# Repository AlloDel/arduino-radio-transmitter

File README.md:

# arduino-radio-transmitter
a simple arduino transmitter designed for an arduino quadcopter designed with kicad 5 and updated for kicad 6

images and PDF of schematic can be found in /docs directory

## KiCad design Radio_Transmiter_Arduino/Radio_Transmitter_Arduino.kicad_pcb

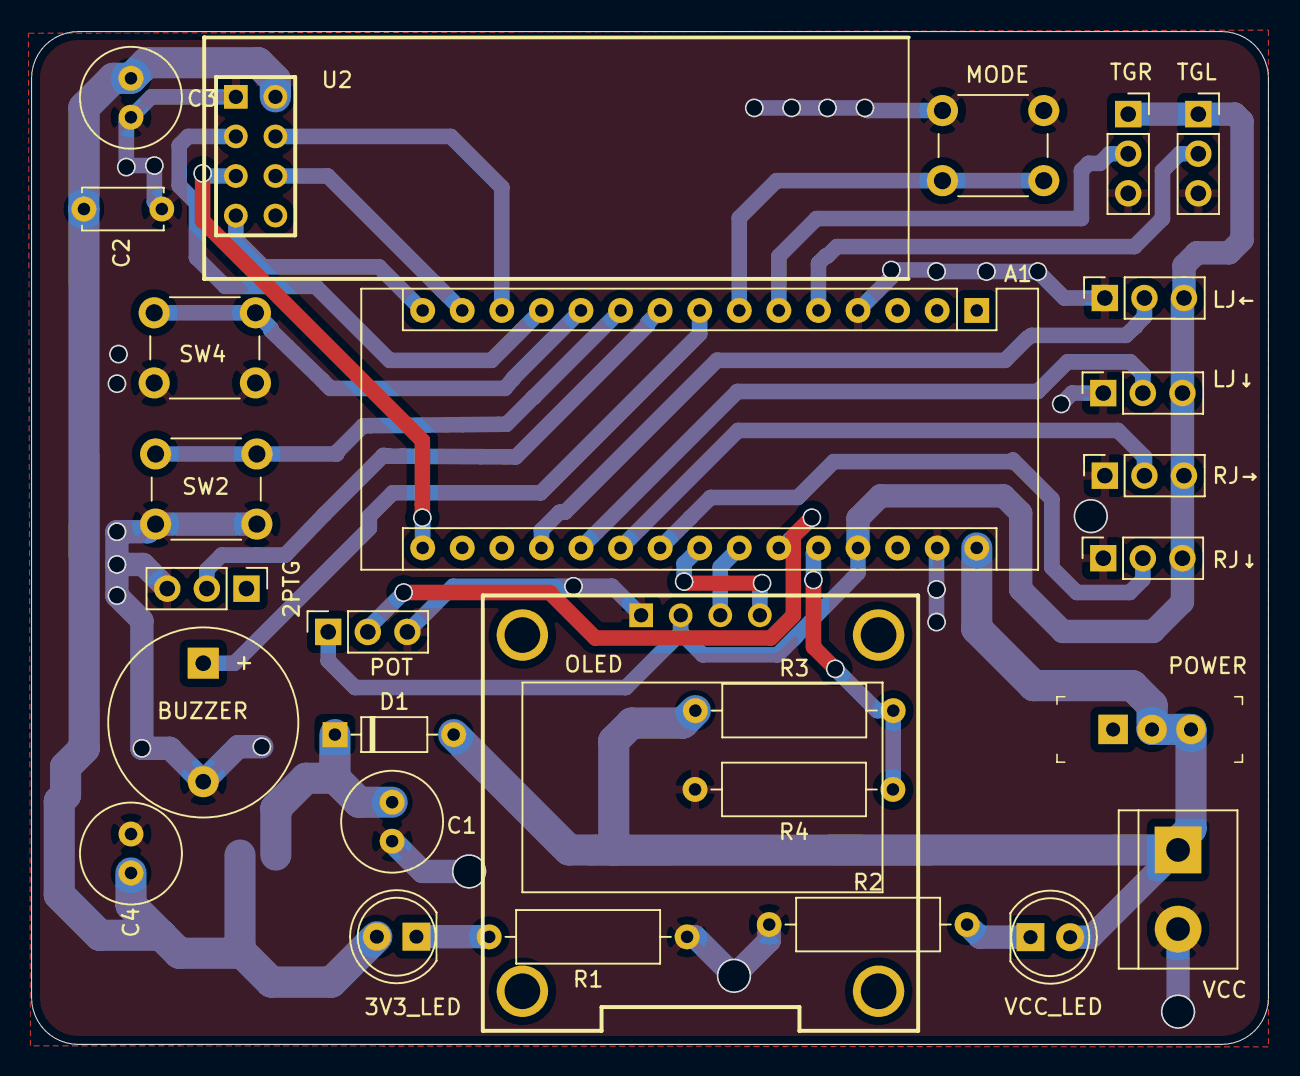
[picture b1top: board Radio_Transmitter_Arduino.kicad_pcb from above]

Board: 2 copper layers, 79.4 x 65.0 mm, 29 parts (1 on the bottom side), 27 nets.

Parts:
2PTG: SW_SPDT; PinHeader_1x03_P2.54mm_Vertical
3V3_LED: Red_LED; LED_D5.0mm_Clear
A1: Arduino_Nano_v3.x; Arduino_Nano
BUZZER: Buzzer; Buzzer_12x9.5RM7.6
C1, C3, C4: 10uF; C_Radial_D6.3mm_H11.0mm_P2.50mm
C2: 100nF; C_Disc_D5.0mm_W2.5mm_P5.00mm
D1: 1N4148; D_DO-35_SOD27_P7.62mm_Horizontal
LJ←: Conn_01x03_Male; PinSocket_1x03_P2.54mm_Vertical
LJ↓: Conn_01x03_Male; PinSocket_1x03_P2.54mm_Vertical
MODE: SW_Push; SW_PUSH_6mm_H13mm
OLED: Conn_01x04_Male; 0.96IN 128X64 I2C OLED DISPLAY MODULE (HOLES)
POT: R_POT; PinSocket_1x03_P2.54mm_Vertical
POWER: EG1218; Switch_Slide_11.6x4mm_EG1218
R1: 220; R_Axial_DIN0309_L9.0mm_D3.2mm_P12.70mm_Horizontal
R2: 330; R_Axial_DIN0309_L9.0mm_D3.2mm_P12.70mm_Horizontal
R3, R4: R_Small; R_Axial_DIN0309_L9.0mm_D3.2mm_P12.70mm_Horizontal
RJ→: Conn_01x03_Male; PinSocket_1x03_P2.54mm_Vertical
RJ↓: Conn_01x03_Male; PinSocket_1x03_P2.54mm_Vertical
SW2, SW4: SW_Push; SW_PUSH_6mm_H13mm
TGL: Conn_01x03_Male; PinSocket_1x03_P2.54mm_Vertical
TGR: Conn_01x03_Male; PinSocket_1x03_P2.54mm_Vertical
U1: AMS1117-3.3; SOT-223-3_TabPin2
U2: NRF24L01_Breakout; NRF24L01+PA+LNA
VCC: Screw_Terminal_01x02; TerminalBlock_bornier-2_P5.08mm
VCC_LED: Green_LED; LED_D5.0mm_Clear

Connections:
+3V3: 3V3_LED.2, C2.1, C3.1, C4.1, U1.2, U2.2
+5V: A1.27, LJ←.3, LJ↓.3, OLED.2, POT.1, RJ→.3, RJ↓.3, TGL.1, TGR.1
/A0: A1.19, LJ←.2
/A1: A1.20, LJ↓.2
/A2: A1.21, RJ→.2
/A3: A1.22, RJ↓.2
/A6: A1.25, POT.2
/BUZZER: A1.8, BUZZER.1
/Battery: A1.26, R3.2, R4.1
/CE: A1.12, U2.3
/CSN: A1.13, U2.4
/D6: 2PTG.2, A1.9
/D7: A1.10, SW2.1
/D8: A1.11, SW4.1
/MISO: A1.15, U2.7
/MODE: A1.7, MODE.2
/MOSI: A1.14, U2.6
/SCK: A1.16, U2.5
/SCL: A1.24, OLED.3
/SDA: A1.23, OLED.4
/ToggleLeft: A1.5, TGL.2
/ToggleRight: A1.6, TGR.2
GND: 2PTG.3, A1.4, A1.29, BUZZER.2, C1.2, C2.2, C3.2, C4.2, LJ←.1, LJ↓.1, MODE.1, OLED.1, POT.3, R1.1, R2.1, R4.2, RJ→.1, RJ↓.1, SW2.2, SW4.2, TGL.3, TGR.3, U1.1, U2.1, VCC.2
unnamed: C1.1, D1.1, U1.3
unnamed: 3V3_LED.1, R1.2
unnamed: R2.2, VCC_LED.1
VCC: A1.30, D1.2, POWER.2, POWER.3, R3.1, VCC.1, VCC_LED.2
